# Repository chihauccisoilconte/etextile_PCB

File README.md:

# EtaxTile board

Editable KiCad 10 working files for an EtaxTile XIAO ESP32-S3 board. The saved PCB is 31.35 × 36.1 mm with 9 footprints and 160 track segments. It does **not** match the saved schematic: the current KiCad check reports 22 schematic-parity issues. These files are not a fabrication release.

Open [`hardware/etaxtile-board.kicad_pro`](hardware/etaxtile-board.kicad_pro) in KiCad. The project-local symbol and footprint libraries live beside it so KiCad can resolve them through `${KIPRJMOD}`.

## Repository guide

| Path | Contents |
| --- | --- |
| [`hardware/`](hardware/) | Editable schematic, PCB, project file, and local libraries |
| [`docs/design-notes.md`](docs/design-notes.md) | Historical design intent, source attribution, and unresolved decisions; not a current build guide |
| [`docs/images/`](docs/images/) | Schematic and PCB previews |
| [`docs/validation/`](docs/validation/) | Current KiCad ERC/DRC reports and generated XML netlist |
| [`scripts/`](scripts/) | Source scripts used to generate the initial design |
| [`STATUS.md`](STATUS.md) | Latest project state and next design decisions |

There is no fabrication package, assembly BOM, or firmware yet. Fabrication and assembly files will be added after the schematic and PCB are reconciled, the parts are selected, and the board is checked for manufacture.

## Editing and reuse

The KiCad files are the editable design sources. The scripts in `scripts/` describe an earlier 125 × 83 mm connector-board concept and do not reproduce the current saved PCB. Both builders refuse to overwrite existing files unless passed `--regenerate`; using that option would overwrite current design work. If developing that older concept separately, `build_schematic.py` writes the schematic and project files, and `build_board.py` reads a KiCad XML netlist at `docs/validation/netlist.xml`.

This repository is a private working draft. No open-source license has been selected or granted. A future public open-source hardware release will need an explicit license, BOM, assembly information, and design files corresponding to a tested revision.

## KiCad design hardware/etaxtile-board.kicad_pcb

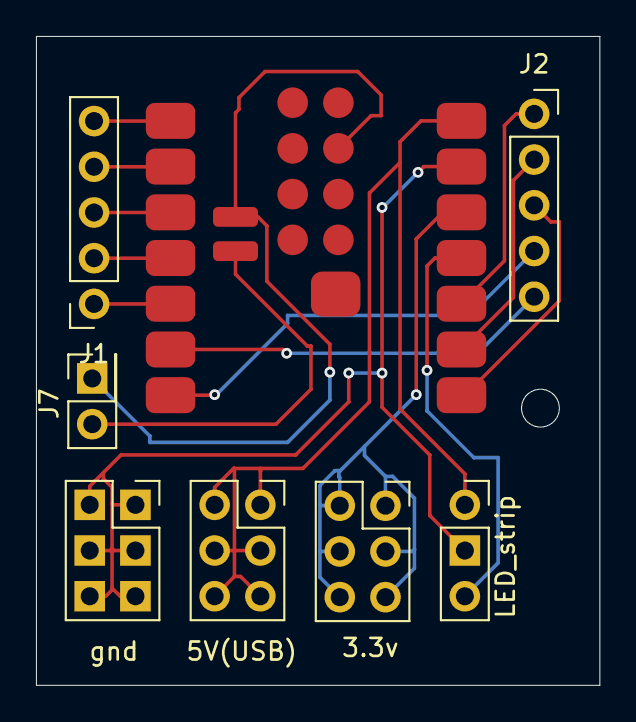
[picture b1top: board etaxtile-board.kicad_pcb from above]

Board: 2 copper layers, 31.3 x 36.0 mm, 8 parts (0 on the bottom side), 15 nets.

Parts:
3.3v, 5V(USB): Conn_01x06_Pin; PinSocket_2x03_P2.54mm_Vertical
J1, J2: Conn_01x05_Socket; PinSocket_1x05_P2.54mm_Vertical
J7: Conn_01x02_Pin; PinSocket_2x01_P2.54mm_Vertical
LED_strip: Conn_01x03_Pin; PinSocket_1x03_P2.54mm_Vertical
U1: Seeed XIAO ESP32-S3; XIAO-ESP32-S3-SMD
gnd: Conn_01x06_Pin; PinSocket_2x03_P2.54mm_Vertical

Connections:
/3V3: 3.3v.1, 3.3v.2, 3.3v.3, 3.3v.4, 3.3v.5, 3.3v.6, U1.12 (3V3_OUT)
/BAT1+: J7.2, U1.23 (BAT1+)
/USB_5V: 5V(USB).1, 5V(USB).2, 5V(USB).3, 5V(USB).4, 5V(USB).5, 5V(USB).6, LED_strip.1, U1.14 (USB_5V)
GND: J7.1, LED_strip.2, U1.13 (GND), U1.18 (GND), U1.24 (GND), gnd.1, gnd.2, gnd.3, gnd.4, gnd.5, gnd.6
unnamed: J1.1, U1.5 (D4/SDA/GPIO5)
unnamed: J1.2, U1.4 (D3/GPIO4)
unnamed: J1.3, U1.3 (D2/GPIO3)
unnamed: J1.4, U1.2 (D1/GPIO2)
unnamed: J1.5, U1.1 (D0/GPIO1)
unnamed: J2.1, U1.10 (D9/GPIO8)
unnamed: J2.2, U1.9 (D8/GPIO7)
unnamed: J2.3, U1.8 (D7/GPIO44)
unnamed: J2.4, U1.7 (D6/GPIO43)
unnamed: J2.5, U1.6 (D5/SCL/GPIO6)
unnamed: LED_strip.3, U1.11 (D10/GPIO9)

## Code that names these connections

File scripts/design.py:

"""EtaxTile connector-first prototype specification; dimensions in mm."""
from pathlib import Path

PROJECT = Path(__file__).resolve().parents[1]
NAME = "etaxtile-board"

# Pin order matches Seeed's XIAO-ESP32-S3-SMD footprint and symbol library.
XIAO_PINS = ["D0/GPIO1", "D1/GPIO2", "D2/GPIO3", "D3/GPIO4",
             "D4/SDA/GPIO5", "D5/SCL/GPIO6", "D6/GPIO43", "D7/GPIO44",
             "D8/GPIO7", "D9/GPIO8", "D10/GPIO9", "3V3_OUT", "GND",
             "USB_5V", "MTDI", "MTDO", "EN", "GND", "MTMS", "MTCK",
             "USB_DN", "USB_DP", "BAT1+", "GND", "PAD"]
XIAO_NETS = [f"D{i}" for i in range(11)] + ["3V3", "GND", "USB_5V"] + [None]*3 + ["GND"] + [None]*4 + ["BAT1+", "GND", None]

PARTS = [
    dict(ref="U1", value="Seeed XIAO ESP32-S3", pins=XIAO_PINS, nets=XIAO_NETS,
         fp="EtaxTile:XIAO-ESP32-S3-SMD", xy=(24, 28), sch=(75, 105), kind="xiao"),
    dict(ref="J1", value="BAT1 1S LiPo", pins=["+", "-"], nets=["BAT1+", "GND"],
         fp="Connector_PinHeader_2.54mm:PinHeader_1x02_P2.54mm_Vertical", xy=(51, 12), sch=(185, 50)),
    dict(ref="J2", value="BAT2 1S LiPo optional", pins=["+", "-"], nets=["BAT2+", "GND"],
         fp="Connector_PinHeader_2.54mm:PinHeader_1x02_P2.54mm_Vertical", xy=(64, 12), sch=(185, 82)),
    dict(ref="J3", value="External 5V boost", pins=["VIN", "GND", "VOUT_5V"], nets=["BOOST_IN", "GND", "BOOST_5V"],
         fp="Connector_PinHeader_2.54mm:PinHeader_1x03_P2.54mm_Vertical", xy=(78, 12), sch=(185, 118)),
    dict(ref="J4", value="Boost input selector", pins=["BAT1", "BOOST_IN", "BAT2"], nets=["BAT1+", "BOOST_IN", "BAT2+"],
         fp="Connector_PinHeader_2.54mm:PinHeader_1x03_P2.54mm_Vertical", xy=(95, 12), sch=(185, 157)),
    dict(ref="J5", value="LED supply selector", pins=["USB_5V", "LED_PWR", "BOOST_5V"], nets=["USB_5V", "LED_PWR", "BOOST_5V"],
         fp="Connector_PinHeader_2.54mm:PinHeader_1x03_P2.54mm_Vertical", xy=(108, 12), sch=(185, 196)),
    dict(ref="J6", value="LED string 1", pins=["V+", "DATA", "GND"], nets=["LED_PWR", "D6", "GND"],
         fp="Connector_PinHeader_2.54mm:PinHeader_1x03_P2.54mm_Vertical", xy=(51, 31), sch=(185, 235)),
    dict(ref="J7", value="LED string 2", pins=["V+", "DATA", "GND"], nets=["LED_PWR", "D7", "GND"],
         fp="Connector_PinHeader_2.54mm:PinHeader_1x03_P2.54mm_Vertical", xy=(64, 31), sch=(185, 274)),
    dict(ref="J8", value="Sensor 1 I2C", pins=["3V3", "GND", "SDA", "SCL"], nets=["3V3", "GND", "D4", "D5"],
         fp="Connector_PinHeader_2.54mm:PinHeader_1x04_P2.54mm_Vertical", xy=(78, 31), sch=(335, 50)),
    dict(ref="J9", value="Sensor 2 GPIO", pins=["3V3", "GND", "SIG_A", "SIG_B"], nets=["3V3", "GND", "D0", "D1"],
         fp="Connector_PinHeader_2.54mm:PinHeader_1x04_P2.54mm_Vertical", xy=(95, 31), sch=(335, 91)),
    dict(ref="J10", value="All XIAO GPIO", pins=[f"D{i}" for i in range(11)], nets=[f"D{i}" for i in range(11)],
         fp="Connector_PinHeader_2.54mm:PinHeader_1x11_P2.54mm_Vertical", xy=(110, 30), sch=(335, 145)),
    dict(ref="J11", value="3V3 / GND expansion", pins=["3V3", "GND"]*4, nets=["3V3", "GND"]*4,
         fp="Connector_PinHeader_2.54mm:PinHeader_1x08_P2.54mm_Vertical", xy=(51, 55), sch=(335, 207)),
    dict(ref="J12", value="LED_PWR / GND expansion", pins=["LED_PWR", "GND"]*3, nets=["LED_PWR", "GND"]*3,
         fp="Connector_PinHeader_2.54mm:PinHeader_1x06_P2.54mm_Vertical", xy=(78, 55), sch=(335, 261)),
    dict(ref="J13", value="USB 5V / GND expansion", pins=["USB_5V", "GND"]*2, nets=["USB_5V", "GND"]*2,
         fp="Connector_PinHeader_2.54mm:PinHeader_1x04_P2.54mm_Vertical", xy=(95, 55), sch=(335, 306)),
]

for part in PARTS:
    assert len(part["pins"]) == len(part["nets"])
